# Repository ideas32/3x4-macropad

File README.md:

# 3x4 macropad

A 3x4 hotswap macropad with per-key rgb, rgb underglow, an oled, and an encoder. Uses the Weact Pi Pico as the microcontroller.
## Features:
- 3x4 array of south-facing MX switches
- hotswap (kailh sockets or equivilant)
- gasket mount
- support for a single 128x32 OLED placed above the microcontroller
- support for a single Alps EC11 rotary encoder
- support for addresable per-key rgb (SK6812 MINI-E) 
- support for addresable rgb underglow (WS2812b)
- through-hole and surface mount diode compatible
- uses a WeAct Studio Pi Pico as the microcontroller 
## Parts List
- 1x Weact Pi Pico
- 1x Alps EC11 encoder
- 12x Kailh or equivilant hotswap sockets
- 14x 1n4148 signal diodes (I prefer through-hole for ease of soldering, but surface mount is also supported)
- 16x M2x3mm screws, preferably with a thin head
- 6x M2x4mm female-female standoffs
- 12x MX-style switches
- 12x MX-style keycaps
- 1x Alps EC11 encoder knob
- 1x PCB, 1.6mm thick
- 1x Plate, 1.6mm thick (I recommend FR4)
- 1x 3d printed Case Top 
- 1x 3d printed Case Bottom 
- 1x 4-6mm thick sheet of foam to make gaskets OR gaskets around 4mm wide by 80mm long by 4-6mm high
- 12x SK6812 Mini-E LEDs (optional)
- 4x WS2812B LEDs (optional)
- 2x 4k7 resistors (only if using OLED)
- 1x SSD1306 128x32 OLED (optional)

Total cost excluding filament, switches, and keycaps when sourced from AliExpress and JLCPCB: ~$50
## Tools Required
- Screwdriver
- Soldering iron, solder, and basic soldering skills (SMD and THT)
- Flush cutters
- QMK source code and knowlege of how to build from source
- 3D printer and filament
# [Build Guide](Build%20Guide.md)

# Notes on the case:
- All filaments except PETG should be ok. I recommend staying away from PETG unless small holes turn out dimensionally accurate (which was not true in my case).
- Bottom case should be printed with transparent filament if using underglow
- Bottom case does require supports, top case does not
- Top case should be printed upside down
- Top case uses 4 M2 heatset inserts
- Assembled using 4x M2x3mm

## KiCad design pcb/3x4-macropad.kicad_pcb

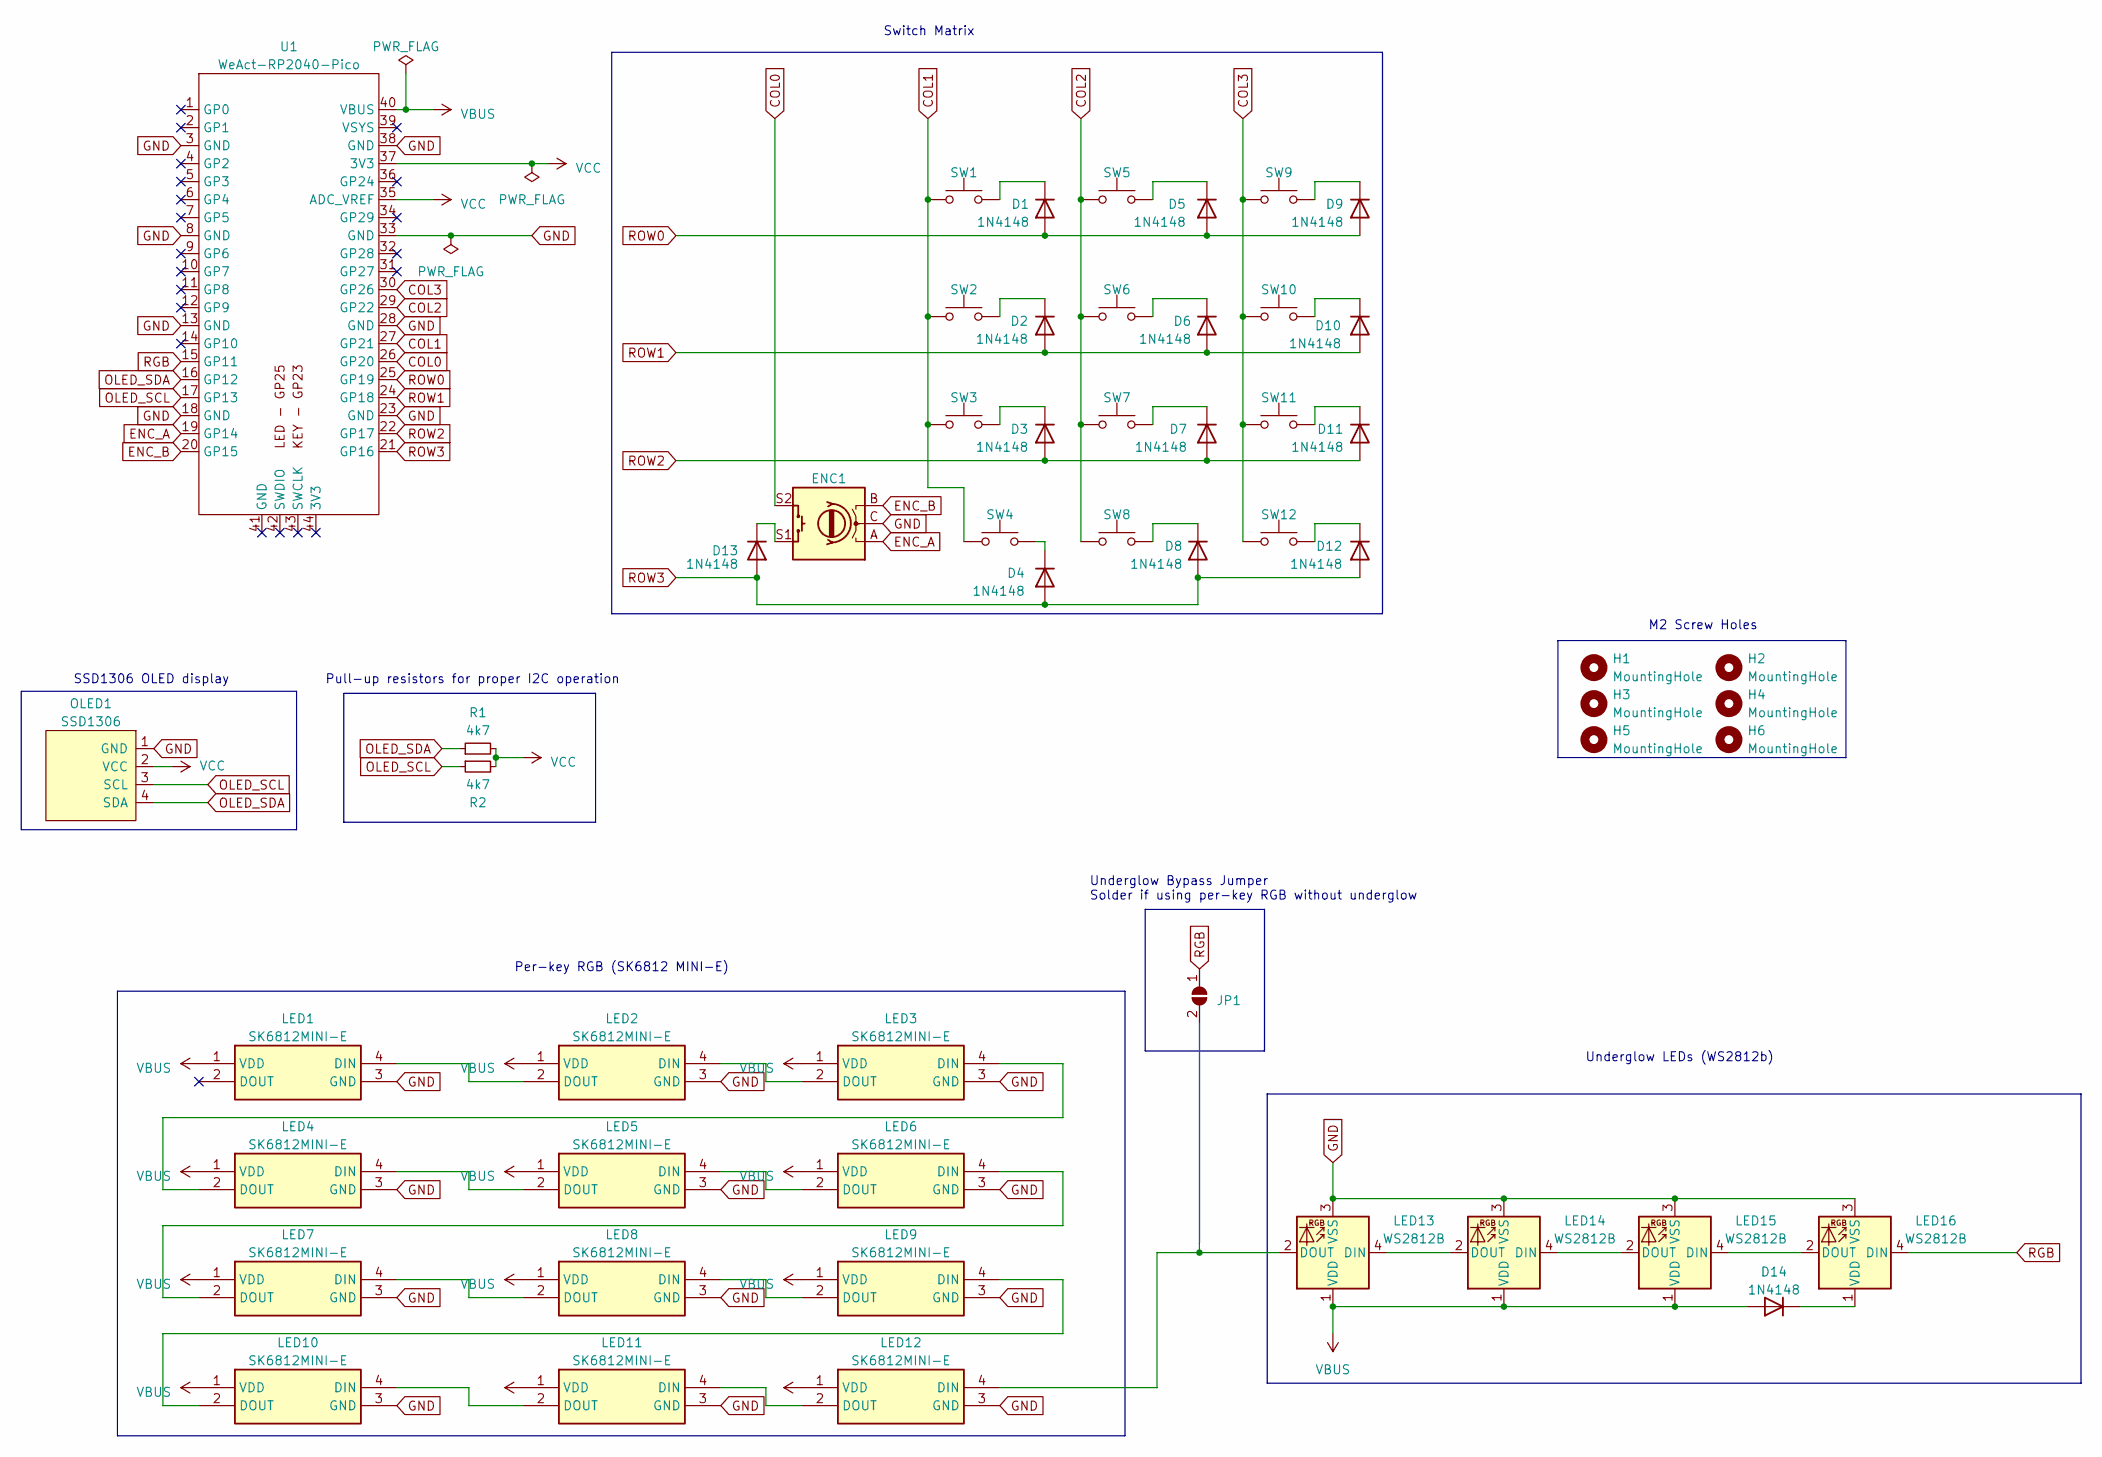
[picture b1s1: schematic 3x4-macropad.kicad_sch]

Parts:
D1, D2, D3, D4, D5, D6, D7, D8, D9, D10, D11, D12, D13, D14: 1N4148; Diode-Hybrid-Back
ENC1: RotaryEncoder_Switch; RotaryEncoder_Alps_EC11E-Switch_Vertical_H20mm
H1, H2, H3, H4, H5, H6: MountingHole; MountingHole_2.2mm_M2_DIN965_Pad_TopBottom
JP1: SolderJumper_2_Open; SolderJumper-2_P1.3mm_Open_RoundedPad1.0x1.5mm
LED1, LED2, LED3, LED4, LED5, LED6, LED7, LED8, LED9, LED10, LED11, LED12: SK6812MINI-E; SK6812-MINI-E; Manufacturer_Part_Number SK6812MINI-E
LED13, LED14, LED15, LED16: WS2812B
OLED1: SSD1306; I2C_Breakout
R1, R2: 4k7; Resistor-Hybrid
SW1, SW2, SW3, SW4, SW5, SW6, SW7, SW8, SW9, SW10, SW11, SW12: SW_Push; MX-Hotswap-1U
U1: WeAct-RP2040-Pico

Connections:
COL0: ENC1.S2, U1.26 (GP20)
COL1: SW1.1, SW2.1, SW3.1, SW4.1, U1.27 (GP21)
COL2: SW5.1, SW6.1, SW7.1, SW8.1, U1.29 (GP22)
COL3: SW9.1, SW10.1, SW11.1, SW12.1, U1.30 (GP26)
ENC_A: ENC1.A, U1.19 (GP14)
ENC_B: ENC1.B, U1.20 (GP15)
GND: ENC1.C, LED1.3 (GND), LED2.3 (GND), LED3.3 (GND), LED4.3 (GND), LED5.3 (GND), LED6.3 (GND), LED7.3 (GND), LED8.3 (GND), LED9.3 (GND), LED10.3 (GND), LED11.3 (GND), LED12.3 (GND), LED13.3 (VSS), LED14.3 (VSS), LED15.3 (VSS), LED16.3 (VSS), OLED1.1 (GND), U1.3 (GND), U1.8 (GND), U1.13 (GND), U1.18 (GND), U1.23 (GND), U1.28 (GND), U1.33 (GND), U1.38 (GND)
unnamed: D1.1 (K), SW1.2
unnamed: D2.1 (K), SW2.2
unnamed: D3.1 (K), SW3.2
unnamed: D4.1 (K), SW4.2
unnamed: D5.1 (K), SW5.2
unnamed: D6.1 (K), SW6.2
unnamed: D7.1 (K), SW7.2
unnamed: D8.1 (K), SW8.2
unnamed: D9.1 (K), SW9.2
unnamed: D10.1 (K), SW10.2
unnamed: D11.1 (K), SW11.2
unnamed: D12.1 (K), SW12.2
unnamed: D13.1 (K), ENC1.S1
unnamed: D14.1 (K), LED16.1 (VDD)
unnamed: JP1.2 (B), LED12.4 (DIN), LED13.2 (DOUT)
unnamed: LED1.4 (DIN), LED2.2 (DOUT)
unnamed: LED2.4 (DIN), LED3.2 (DOUT)
unnamed: LED3.4 (DIN), LED4.2 (DOUT)
unnamed: LED4.4 (DIN), LED5.2 (DOUT)
unnamed: LED5.4 (DIN), LED6.2 (DOUT)
unnamed: LED6.4 (DIN), LED7.2 (DOUT)
unnamed: LED7.4 (DIN), LED8.2 (DOUT)
unnamed: LED8.4 (DIN), LED9.2 (DOUT)
unnamed: LED10.4 (DIN), LED11.2 (DOUT)
unnamed: LED9.4 (DIN), LED10.2 (DOUT)
unnamed: LED11.4 (DIN), LED12.2 (DOUT)
unnamed: LED13.4 (DIN), LED14.2 (DOUT)
unnamed: LED14.4 (DIN), LED15.2 (DOUT)
unnamed: LED15.4 (DIN), LED16.2 (DOUT)
OLED_SCL: OLED1.3 (SCL), R2.1, U1.17 (GP13)
OLED_SDA: OLED1.4 (SDA), R1.1, U1.16 (GP12)
RGB: JP1.1 (A), LED16.4 (DIN), U1.15 (GP11)
ROW0: D1.2 (A), D5.2 (A), D9.2 (A), U1.25 (GP19)
ROW1: D2.2 (A), D6.2 (A), D10.2 (A), U1.24 (GP18)
ROW2: D3.2 (A), D7.2 (A), D11.2 (A), U1.22 (GP17)
ROW3: D4.2 (A), D8.2 (A), D12.2 (A), D13.2 (A), U1.21 (GP16)
VBUS: D14.2 (A), LED1.1 (VDD), LED2.1 (VDD), LED3.1 (VDD), LED4.1 (VDD), LED5.1 (VDD), LED6.1 (VDD), LED7.1 (VDD), LED8.1 (VDD), LED9.1 (VDD), LED10.1 (VDD), LED11.1 (VDD), LED12.1 (VDD), LED13.1 (VDD), LED14.1 (VDD), LED15.1 (VDD), U1.40 (VBUS)
VCC: OLED1.2 (VCC), R1.2, R2.2, U1.35 (ADC_VREF), U1.37 (3V3)

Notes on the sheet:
Switch Matrix
Per-key RGB (SK6812 MINI-E)
Underglow LEDs (WS2812b)
Pull-up resistors for proper I2C operation
M2 Screw Holes
Underglow Bypass Jumper Solder if using per-key RGB without underglow
SSD1306 OLED display

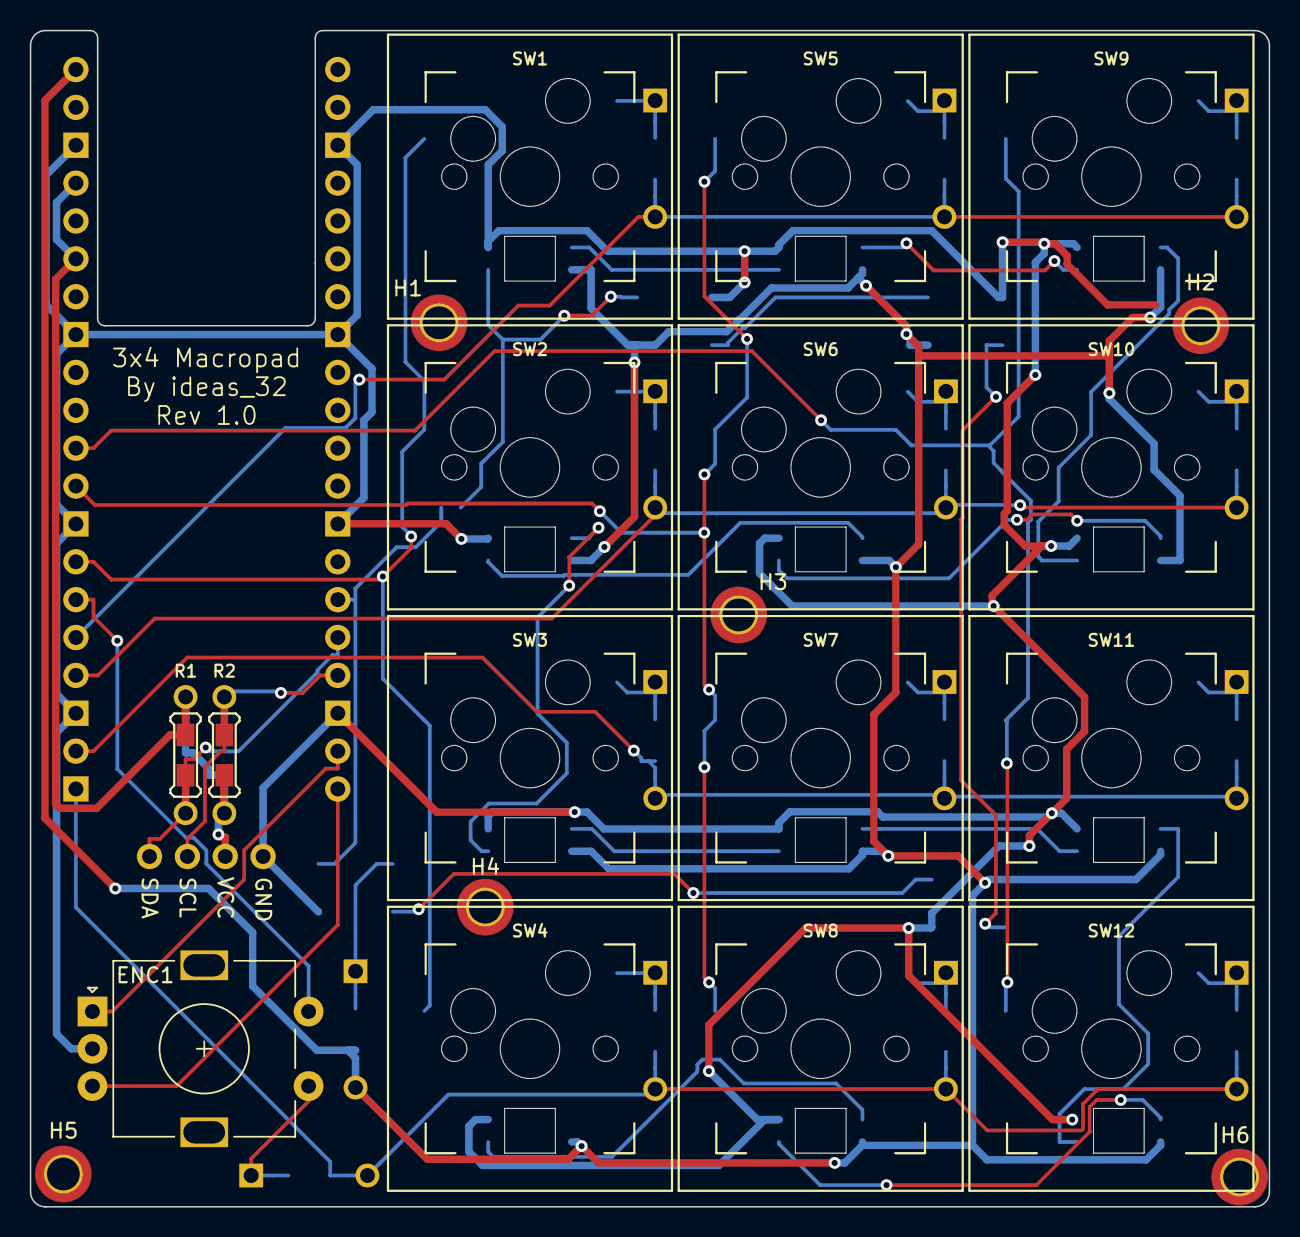
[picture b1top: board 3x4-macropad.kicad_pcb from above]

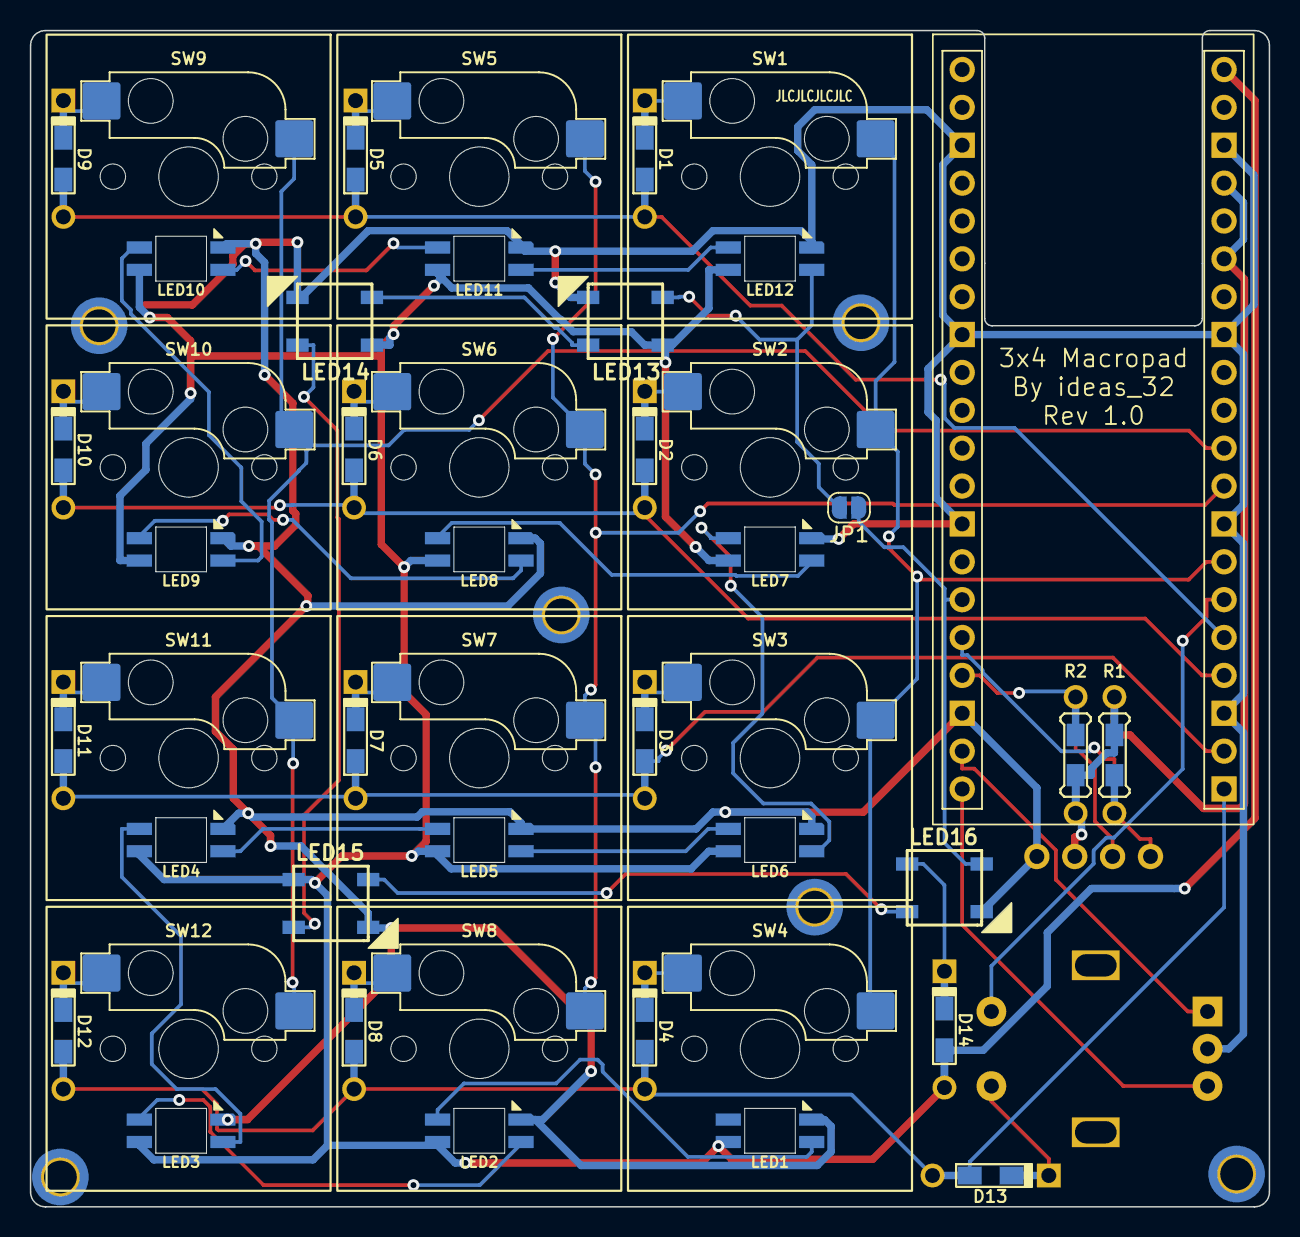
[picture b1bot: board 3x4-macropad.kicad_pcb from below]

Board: 2 copper layers, 83.1 x 78.9 mm, 54 parts (34 on the bottom side), 45 nets.

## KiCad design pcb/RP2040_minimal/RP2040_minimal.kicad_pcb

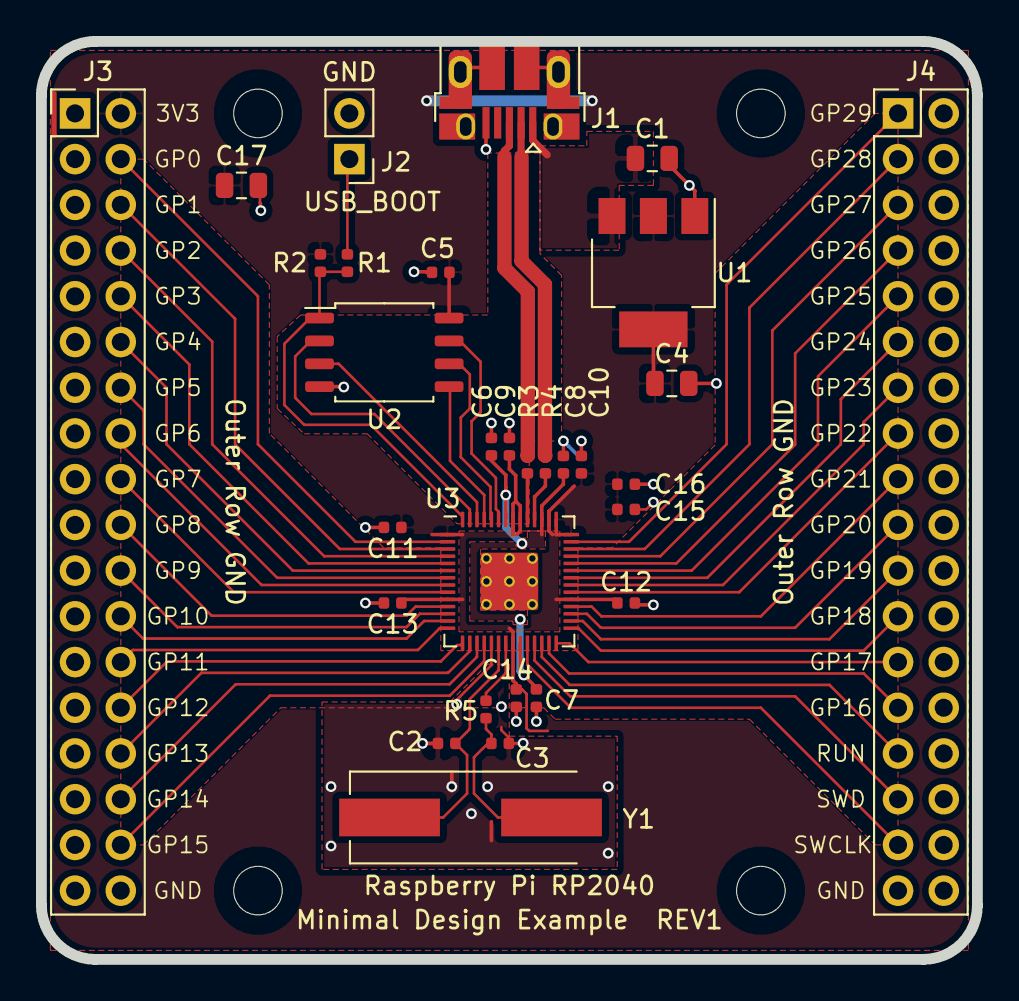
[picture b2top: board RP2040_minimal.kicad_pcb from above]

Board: 2 copper layers, 52.0 x 51.0 mm, 34 parts (0 on the bottom side), 51 nets.

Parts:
C1, C4, C17: 10u; C_0805_2012Metric
C2, C3: 27p; C_0402_1005Metric
C5, C6, C7, C9, C11, C12, C13, C14, C15, C16: 100n; C_0402_1005Metric
C8, C10: 1u; C_0402_1005Metric
H1, H2, H3, H4: MountingHole; MountingHole_2.7mm_M2.5
J1: USB_B_Micro; USB_Micro-B_Amphenol_10103594-0001LF_Horizontal_modified
J2: Conn_01x02; PinHeader_1x02_P2.54mm_Vertical
J3, J4: Conn_02x18_Odd_Even; PinHeader_2x18_P2.54mm_Vertical
R1, R5: 1k; C_0402_1005Metric
R2: DNF; C_0402_1005Metric
R3, R4: 27; C_0402_1005Metric
U1: NCP1117-3.3_SOT223; SOT-223-3_TabPin2
U2: W25Q128JVS; SOIC-8_5.23x5.23mm_P1.27mm
U3: RP2040; RP2040-QFN-56
Y1: ABLS-12.000MHZ-B4-T; Crystal_SMD_HC49-US

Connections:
+1V1: C6.1, C7.1, C8.1, U3.23, U3.45, U3.50
+3V3: C4.1, C5.1, C9.1, C10.1, C11.1, C12.1, C13.1, C14.1, C15.1, C16.1, C17.1, J3.2, R2.1, U1.2, U2.8, U3.1, U3.10, U3.22, U3.33, U3.42, U3.43, U3.44, U3.48, U3.49
/GPIO0: J3.4, U3.2
/GPIO1: J3.6, U3.3
/GPIO2: J3.8, U3.4
/GPIO3: J3.10, U3.5
/GPIO4: J3.12, U3.6
/GPIO5: J3.14, U3.7
/GPIO6: J3.16, U3.8
/GPIO7: J3.18, U3.9
/GPIO8: J3.20, U3.11
/GPIO9: J3.22, U3.12
/GPIO10: J3.24, U3.13
/GPIO11: J3.26, U3.14
/GPIO12: J3.28, U3.15
/GPIO13: J3.30, U3.16
/GPIO14: J3.32, U3.17
/GPIO15: J3.34, U3.18
/GPIO16: J4.27, U3.27
/GPIO17: J4.25, U3.28
/GPIO18: J4.23, U3.29
/GPIO19: J4.21, U3.30
/GPIO20: J4.19, U3.31
/GPIO21: J4.17, U3.32
/GPIO22: J4.15, U3.34
/GPIO23: J4.13, U3.35
/GPIO24: J4.11, U3.36
/GPIO25: J4.9, U3.37
/GPIO26_ADC0: J4.7, U3.38
/GPIO27_ADC1: J4.5, U3.39
/GPIO28_ADC2: J4.3, U3.40
/GPIO29_ADC3: J4.1, U3.41
/QSPI_SCLK: U2.6, U3.52
/QSPI_SD0: U2.5, U3.53
/QSPI_SD1: U2.2, U3.55
/QSPI_SD2: U2.3, U3.54
/QSPI_SD3: U2.7, U3.51
/QSPI_SS: R1.1, R2.2, U2.1, U3.56
/RUN: J4.29, U3.26
/SWCLK: J4.33, U3.24
/SWD: J4.31, U3.25
/USB_D+: J1.3, R3.1
/USB_D-: J1.2, R4.1
/XIN: C2.1, U3.20, Y1.1
/XOUT: R5.1, U3.21
/~USB_BOOT: J2.1, R1.2
GND: C1.2, C2.2, C3.2, C4.2, C5.2, C6.2, C7.2, C8.2, C9.2, C10.2, C11.2, C12.2, C13.2, C14.2, C15.2, C16.2, C17.2, J1.5, J1.6, J2.2, J3.1, J3.3, J3.5, J3.7, J3.9, J3.11, J3.13, J3.15, J3.17, J3.19, J3.21, J3.23, J3.25, J3.27, J3.29, J3.31, J3.33, J3.35, J3.36, J4.2, J4.4, J4.6, J4.8, J4.10, J4.12, J4.14, J4.16, J4.18, J4.20, J4.22, J4.24, J4.26, J4.28, J4.30, J4.32, J4.34, J4.35, J4.36, U1.1, U2.4, U3.19, U3.57
unnamed: C3.1, R5.2, Y1.2
unnamed: R3.2, U3.47
unnamed: R4.2, U3.46
VBUS: C1.1, J1.1, U1.3

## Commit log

2023-04-28 Initial Revision of case and pcb
2023-04-28 Updated README.md and pcb with jlcpcb clearance requirements
2023-05-03 changed silkscreen reference for the pi pico footprint
2023-05-04 Update README.md
    tested the case and wrote a to do list
2023-05-06 stuff
    - cleaned up routing
    - changed per-key rgb footprint
    - changed resistor footprint
    - changed diode footprint to actually support sod123
    - made power traces 0.5mm
2023-05-10 Init rp2040 on board
2023-05-16 Updates and QOL
    - changed revision silkscreen text
    - removed silkscreen on diode pads
    - updated readme.md
    - ready for rev 0.2
2023-05-17 v0.2
    - bugfixes mostly
    - changed case to 4 part for cleaner print
2023-05-18 update gerbers
2023-05-22 flipped pi pico
    - boot is still accessible because of cutout in board
2023-09-25 remove outdated case files
2023-09-26 V0.2 changed to gasket mount, added plate file, modified pcb to fix bugs
2023-09-26 Initial release
    Combination of many bugfixes, finally commiting the plate, and updating the silkscreen text
2023-11-06 Fixed Bugs
2023-12-29 Removed zone that made ground pads hard to solder
2024-01-02 Documentation and plate update
2024-01-02 Add case files
